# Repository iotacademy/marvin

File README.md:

# Marvin

## Hi!!!!

Hello there! Cool of you to made your way here! The whole Marvin team is very excited and welcomes everyone (including you!) to join us in developing awesome/funny/usefull/insightfull or complete bonkers useless gadgets in the world of IoT.

## About Marvin

Marvin is easy to use, Arduino based, plug and play grove sensor compatible and works with LoRa communication on the KPN nation covering LoRa network.

Please check our [Kickstarter campaign](https://www.kickstarter.com/projects/688158475/marvin-the-lora-development-board/), the possibilities at the [IoTAcademy](http://iotacademy.nl) and the [RDM Makerspace](http://www.rdmmakerspace.nl/cursussen/internet-of-things).

## What are you doing here?!

Okay that may have come of a bit harsh. We *do* welcome you, but you are kinda on a junction here.

Are you interested in:

[Software](https://github.com/iotacademy/marvin/tree/master/Software)?

or 

[Hardware](https://github.com/iotacademy/marvin/tree/master/Hardware)?

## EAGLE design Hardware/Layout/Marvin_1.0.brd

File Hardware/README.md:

# Marvin Hardware
This overview contains documentation regarding the hardware used in Marvin. 

##General
The Marvin consists of 4 main features: A USB port, Arduino compatible microcontroller, 5 Grove connectors and a LoRa(WAN) modem. The board is optimized to be used for quick and easy applications in R&D and workshops, as well as a very reasonable solution for embedded applications.

##ATMEGA32u4

##Grove connectors
The 5 grove connectors cover all analog(x3), digital(x1) and I2C(x1). The I2C port can also be used as a digital input/output.

##ISP
The 2x3 male header is used to burn the bootloader on the microcontroller. As this is done via SPI, this bus is available for other SPI peripherals. On the bottom there are an additional 6 contact pads using pogo pins instead of a 2x3 wired connector.

##Serial
The RX/TX pins from the microcontroller are available via an unpopulated connection. The LoRa modem is controlled over the same line, so it needs to be shut down when other UART devices are used to prevent errors.

##GPIO
Next to the Grove connectors there is another two unpopulated connection point, connected to GPIO 8 and 9 of the LoRa module.

##Antenna
The antenna is a 868MHz ceramic resonator antenna with a pigtail behind it. The choice to go for a ceramic antenna (instead of the regular antenna on SMA connector that is spec'd) was done for two reasons, the on-pcb ceramic antenna is a lot smaller and less fragile, and in our side-by-side tests the ceramic antenna performed considerably better on all scores.

##USB
The full size USB plug and the micro USB are linked directly together. The full size connector is used for plugging it right in your laptop, the micro USB can be used when the unit is embedded in a place where is not easily removeable and makes the system a lot more flexible.

##Level shifters
The microcontroller and the LoRa modem work at different voltages (5v&3.3V), so for the communication and reset lines there are level shifters in place. 

##Dimensions
The overal dimensions of the PCB are 85x30mm and the pcb is 2.4mm thick. This thickness is required to make the PCB fit the usb port.

##Board and Schematics
See Layout folder.

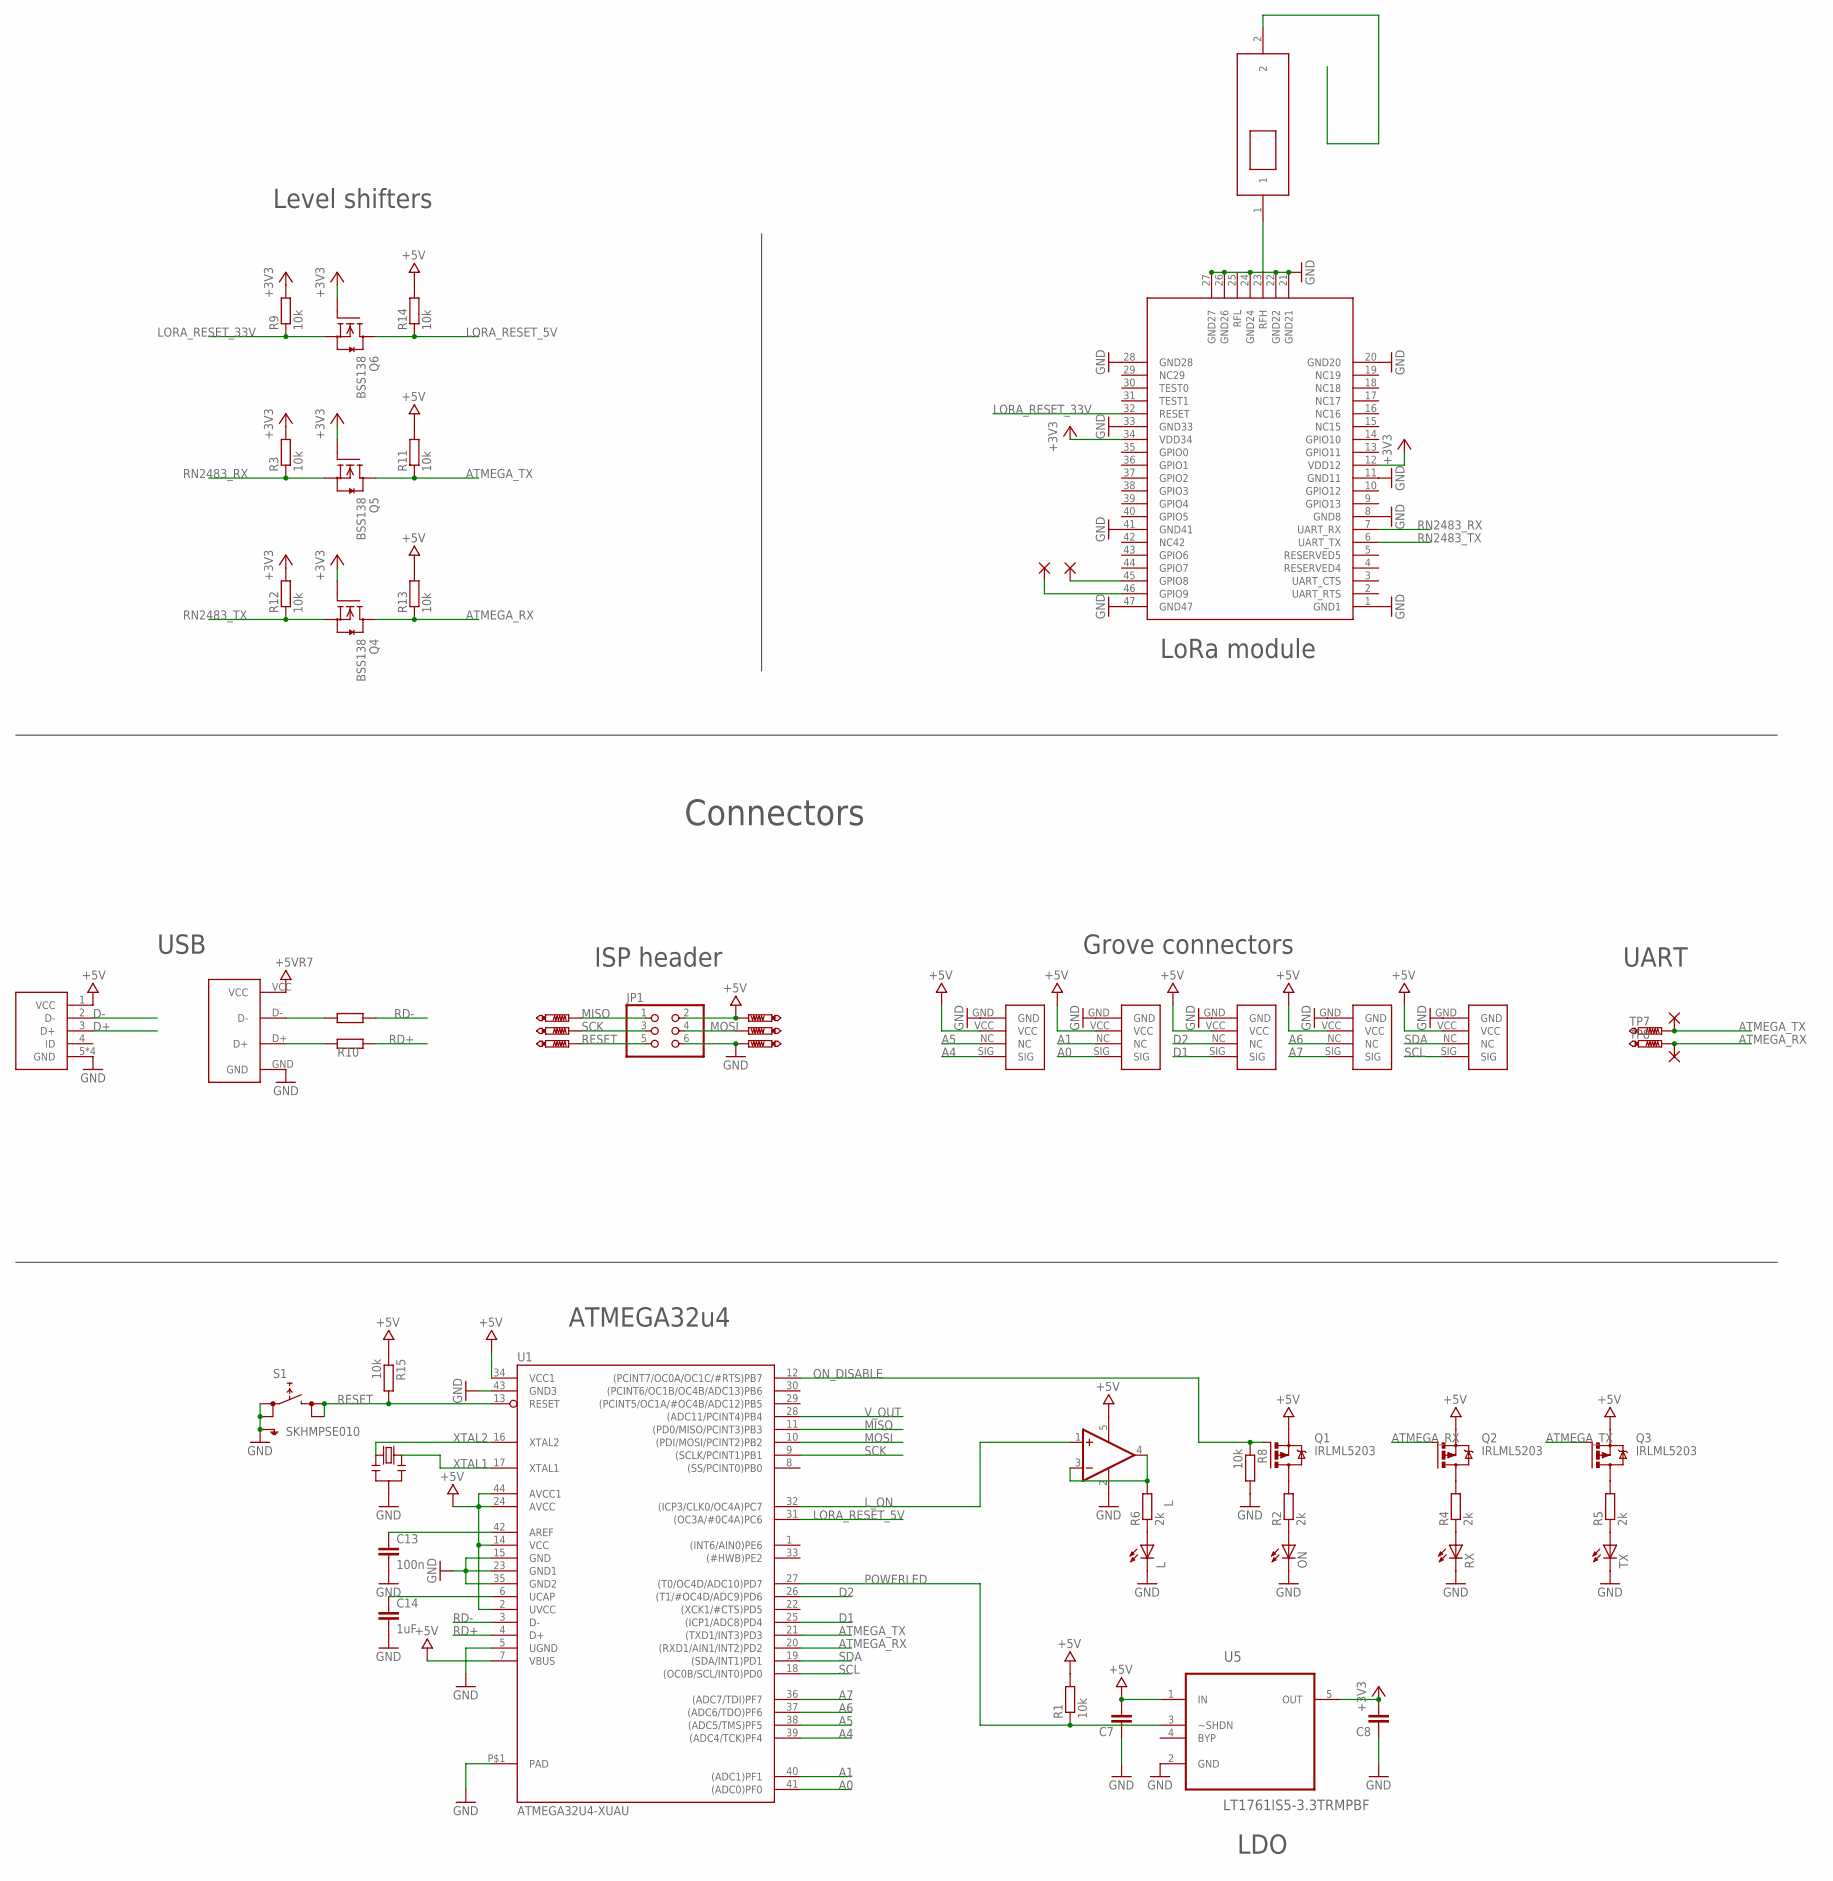
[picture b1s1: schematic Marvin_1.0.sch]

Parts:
A1, A2, A3: GROVE; 4POS2MM
C7, C8: C-EUC0603; C0603
C13: 100n; C0603K
C14: 1uF; C0603K
D2, D2/I2C: GROVE; 4POS2MM
IC1: LM321MF; SOT23-5
JP1: PINHD-2X3; 2X03
L: LEDSML0603; SML0603
ON: LEDSML0603; SML0603
PAD1, PAD2, PAD3, PAD4: WIREPAD1,6/0,9; 1,6/0,9
Q1, Q2, Q3: IRLML5203; MICRO3
Q4, Q5, Q6: BSS138; SOT23
R1, R3, R8, R9, R11, R12, R13, R14, R15: 10k; R0603
R2, R4, R5, R6: 2k; R0603
R7, R10: 30; R0603-ROUND
RX: LEDSML0603; SML0603
S1: SKHMPSE010; SKHMPXE010
TP1, TP2, TP3, TP4, TP5, TP6, TP7, TP8: PTR1B1,27; B1,27
TX: LEDSML0603; SML0603
U1: ATMEGA32U4-XUAU; TQFP44-PAD
U5: LT1761IS5-3.3TRMPBF; SOT95P280X100-5N
U$1: RN2483
U$3: USBA; USBAPLUG
U$16: USB-VERTICAL; MICROUSBVERTICAL
U$25: 868AT
Y1: CSTCE16M0V53-R0 16MHZ; RESONATOR

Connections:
+3V3: C8.2, Q4.1 (G), Q5.1 (G), Q6.1 (G), R3.2, R9.2, R12.2, U5.5 (OUT), U$1.12 (VDD12), U$1.34 (VDD34)
+5V: A1.VCC, A2.VCC, A3.VCC, C7.2, D2.VCC, D2/I2C.VCC, IC1.5 (V+), JP1.2, Q1.2 (S), Q2.2 (S), Q3.2 (S), R1.2, R11.2, R13.2, R14.2, R15.1, TP6.TP, U1.2 (UVCC), U1.7 (VBUS), U1.14 (VCC), U1.24 (AVCC), U1.34 (VCC1), U1.44 (AVCC1), U5.1 (IN), U$3.VCC, U$16.1 (VCC)
A0: A1.SIG, U1.41 ((ADC0)PF0)
A1: A1.NC, U1.40 ((ADC1)PF1)
A4: A2.SIG, U1.39 ((ADC4/TCK)PF4)
A5: A2.NC, U1.38 ((ADC5/TMS)PF5)
A6: A3.NC, U1.37 ((ADC6/TDO)PF6)
A7: A3.SIG, U1.36 ((ADC7/TDI)PF7)
AREF1: C13.1, U1.42 (AREF)
ATMEGA_RX: PAD2.1, Q2.1 (G), Q4.3 (D), R13.1, TP8.TP, U1.20 ((RXD1/AIN1/INT2)PD2)
ATMEGA_TX: PAD1.1, Q3.1 (G), Q5.3 (D), R11.1, TP7.TP, U1.21 ((TXD1/INT3)PD3)
D1: D2.SIG, U1.25 ((ICP1/ADC8)PD4)
D2: D2.NC, U1.26 ((T1/#OC4D/ADC9)PD6)
D+: R10.2, U$3.D+, U$16.3 (D+)
D-: R7.2, U$3.D-, U$16.2 (D-)
GND: A1.GND, A2.GND, A3.GND, C7.1, C8.1, C13.2, C14.2, D2.GND, D2/I2C.GND, IC1.2 (V-), JP1.6, L.C, ON.C, R8.2, RX.C, S1.1 (1.1), S1.2 (1.2), S1.5 (SH), TP4.TP, TX.C, U1.5 (UGND), U1.15 (GND), U1.23 (GND1), U1.35 (GND2), U1.43 (GND3), U1.P$1 (PAD), U5.2 (GND), U$1.1 (GND1), U$1.8 (GND8), U$1.11 (GND11), U$1.20 (GND20), U$1.21 (GND21), U$1.22 (GND22), U$1.24 (GND24), U$1.26 (GND26), U$1.27 (GND27), U$1.28 (GND28), U$1.33 (GND33), U$1.41 (GND41), U$1.47 (GND47), U$3.GND, U$16.5 (GND), U$16.P$1 (GND), U$16.P$2 (GND), U$16.P$3 (GND), Y1.2
L: IC1.3 (-IN), IC1.4 (OUT), R6.2
LORA_RESET_5V: Q6.3 (D), R14.1, U1.31 ((OC3A/#0C4A)PC6)
LORA_RESET_33V: Q6.2 (S), R9.1, U$1.32 (RESET)
L_ON: IC1.1 (+IN), U1.32 ((ICP3/CLK0/OC4A)PC7)
MISO: JP1.1, TP1.TP, U1.11 ((PD0/MISO/PCINT3)PB3)
MOSI: JP1.4, TP5.TP, U1.10 ((PDI/MOSI/PCINT2)PB2)
unnamed: ON.A, R2.1
unnamed: R4.1, RX.A
unnamed: R5.1, TX.A
unnamed: L.A, R6.1
unnamed: Q1.3 (D), R2.2
unnamed: PAD3.1, U$1.46 (GPIO9)
unnamed: Q2.3 (D), R4.2
unnamed: Q3.3 (D), R5.2
unnamed: PAD4.1, U$1.45 (GPIO8)
ON_DISABLE: Q1.1 (G), R8.1, U1.12 ((PCINT7/OC0A/OC1C/#RTS)PB7)
POWERLED: R1.1, U1.27 ((T0/OC4D/ADC10)PD7), U5.3 (~SHDN)
RD+: R10.1, U1.4 (D+)
RD-: R7.1, U1.3 (D-)
RESET: JP1.5, R15.2, S1.3 (2.1), S1.4 (2.2), TP3.TP, U1.13 (RESET)
RFH: U$1.23 (RFH), U$25.1
RN2483_RX: Q5.2 (S), R3.1, U$1.7 (UART_RX)
RN2483_TX: Q4.2 (S), R12.1, U$1.6 (UART_TX)
SCK: JP1.3, TP2.TP, U1.9 ((SCLK/PCINT1)PB1)
SCL: D2/I2C.SIG, U1.18 ((OC0B/SCL/INT0)PD0)
SDA: D2/I2C.NC, U1.19 ((SDA/INT1)PD1)
UCAP: C14.1, U1.6 (UCAP)
V_OUT: U1.28 ((ADC11/PCINT4)PB4)
XTAL1: U1.17 (XTAL1), Y1.3
XTAL2: U1.16 (XTAL2), Y1.1

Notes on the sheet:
Grove connectors
LoRa module
LDO
USB
Level shifters
ATMEGA32u4
ISP header
UART
Connectors

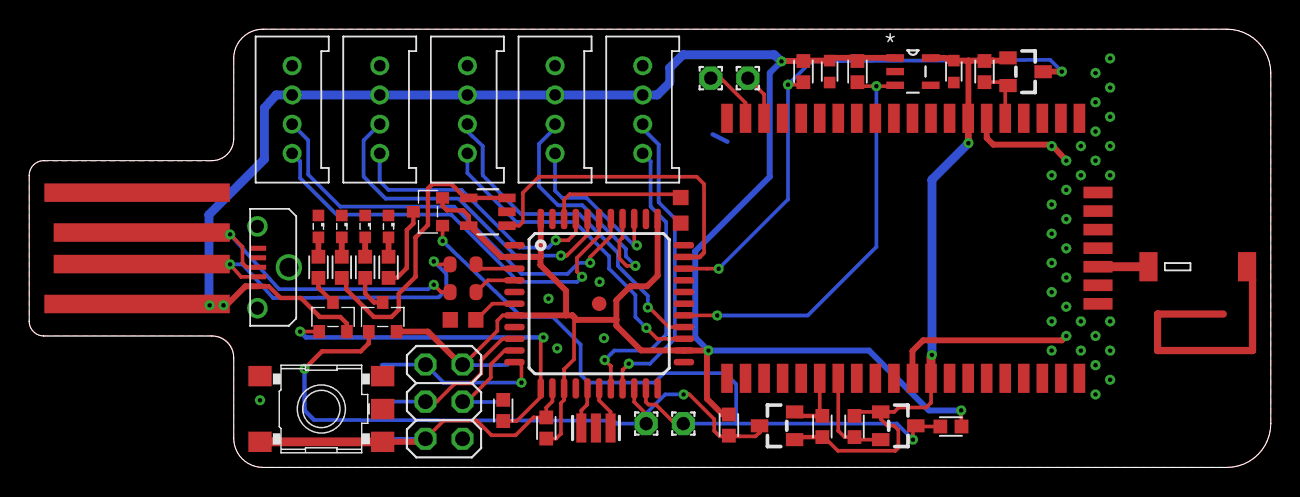
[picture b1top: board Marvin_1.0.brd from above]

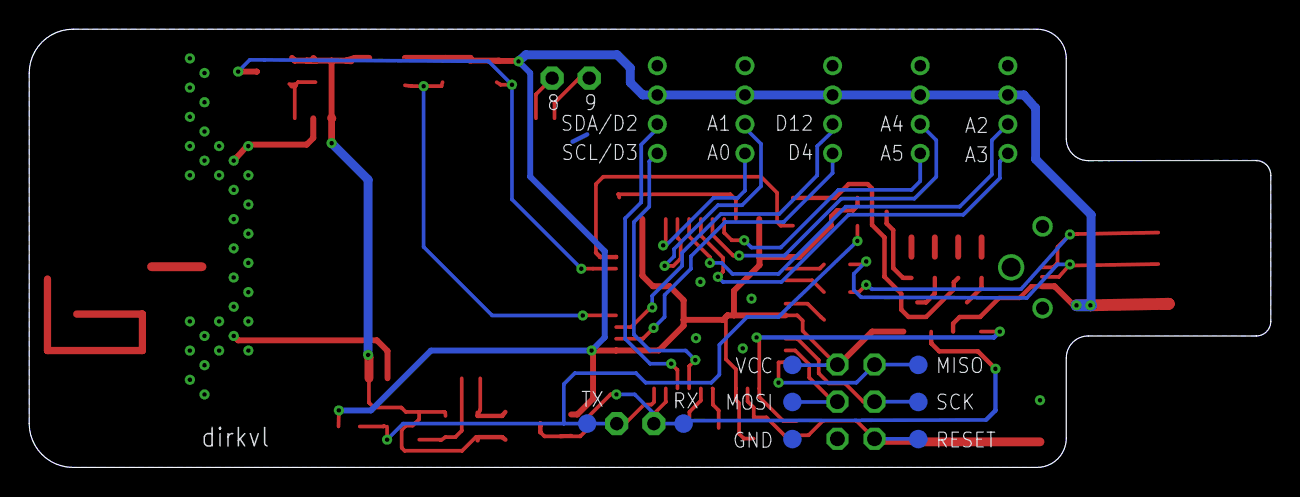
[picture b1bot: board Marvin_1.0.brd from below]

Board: 2 copper layers, 85.0 x 30.0 mm, 56 parts (8 on the bottom side), 45 nets.

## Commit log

2016-07-08 Basic controls of IoT Academy Marvin LoRa Development board
    This version supports:
    - Sending LoRa uplink messages using ABP
    - Blink three times when sending data
2016-07-08 Rename MultiSerialMarvin.ino to 2. MultiSerialMarvin.ino
2016-07-08 Rename MarvinBlink.ino to 1. MarvinBlink.ino
2016-07-08 Rename MarvinBase.ino to 3. MarvinBase.ino
2016-07-08 Rename 2. MultiSerialMarvin.ino to 2. MarvinMultiSerial.ino
2016-07-11 No space, point and number in filename
2016-07-14 Added comments and support for powering on/off
2016-07-14 Added Powering up Marvin
2016-08-14 Adding eagle layout
    board and schematic
2016-08-14 pics
2016-08-14 brd updates
2016-09-04 Update MarvinBase.ino
    Some minor changes.
    -Using led_port instead of hardcoded 13.
    -Using declared defaultBaudRate, also changed to long.
    -Changed order in function: initializeRN2483, order was sys,mac radio. Now: sys, radio, mac
    -Description of set_port changed
2016-09-09 Added extra text
2016-09-09 Created MarvinLaptop
    Enter hexadecimal input through your serial as payload.
2016-09-09 Added folders to enable running from Arduino IDE directly
2016-09-11 Added MarinPhoto with port-layout
2016-09-11 Changed README
2016-09-13 increased delay send
2016-10-30 cleaning up pcb
2016-11-01 dimensions
2016-11-01 resizing
2016-11-01 moar pics
2016-11-01 antenna
2016-11-01 levelshift
2016-11-01 intro
2016-11-01 readme
2016-11-12 sw stuff
2016-11-12 pics edit
2016-11-14 pinout
2016-11-14 resize
2016-11-14 rxtx
2016-11-14 fix link
2017-03-14 Added sensor read
    Read float value, cast to int and send in string as lorapayload
2017-03-27 Update documentation
    Updated documentation for pin selection and sending temperature value as
    integer or multiplied
2017-03-27 Update discription
2017-03-27 Added link to seeed wiki
    Link to seeedstudio wiki page for grove temperature v1.2
2017-03-27 Added arduino file for Temp+humid sensor from Grove
    You have to download the dht library from
    http://wiki.seeed.cc/Grove-Temperature_and_Humidity_Sensor_Pro/
2017-03-27 Added link to seeedstudio github for library temp&humid sensor
2017-03-27 Fixed error temp sent twice + added delimiter
    The temperature was sent twice, fixed so temp and humidity are being sent.
    Also added delimiter between te two values, because, although humidity usually is 2 digits, it is better not to rely on that.
    Since the delimiter had to be an acceptable HEX value I choose "F"
2017-03-28 Changed lora message
    send temperature / humidity rounded
    or send temp / hum as 4 digit
2017-03-28 Forgot to add delimiter F
2017-06-09 Added Hackaton Ino File
    Setting Cayenne low power payload
2017-06-10 Remove abp folder due to sync issues
2017-06-10 adding formatter for clearblade
2017-06-10 Adding gps
2017-06-10 Update gps code
2017-06-10 Updating things
2017-06-10 change default cnf mesage
2017-06-21 Fix Markdown syntax for titles ;)
2017-06-24 update temperature humidity code
2017-08-03 Corrected heading by adding a space after ##
2017-08-03 Changed spaced to tabs of Software/MarvinBase/MarvinBase.ino
2017-08-04 Rewritten code for Marvin. Put all LoRa related code into a class.
2017-08-04 Made the Marvin library in a seperate folder for better maintainability. Adjusted README for this and MarvinBase.
2017-08-04 Applied the new Marvin lib to every program.
2017-08-04 Forgot to set LoRa module actually on when using powerOn()
2018-03-07 Create readmy
2018-03-07 Rename Readme to Readme.md

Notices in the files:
parts and their libraries:
m-pad-2.1: License : GNU General Public License version 2 (see bottom)
